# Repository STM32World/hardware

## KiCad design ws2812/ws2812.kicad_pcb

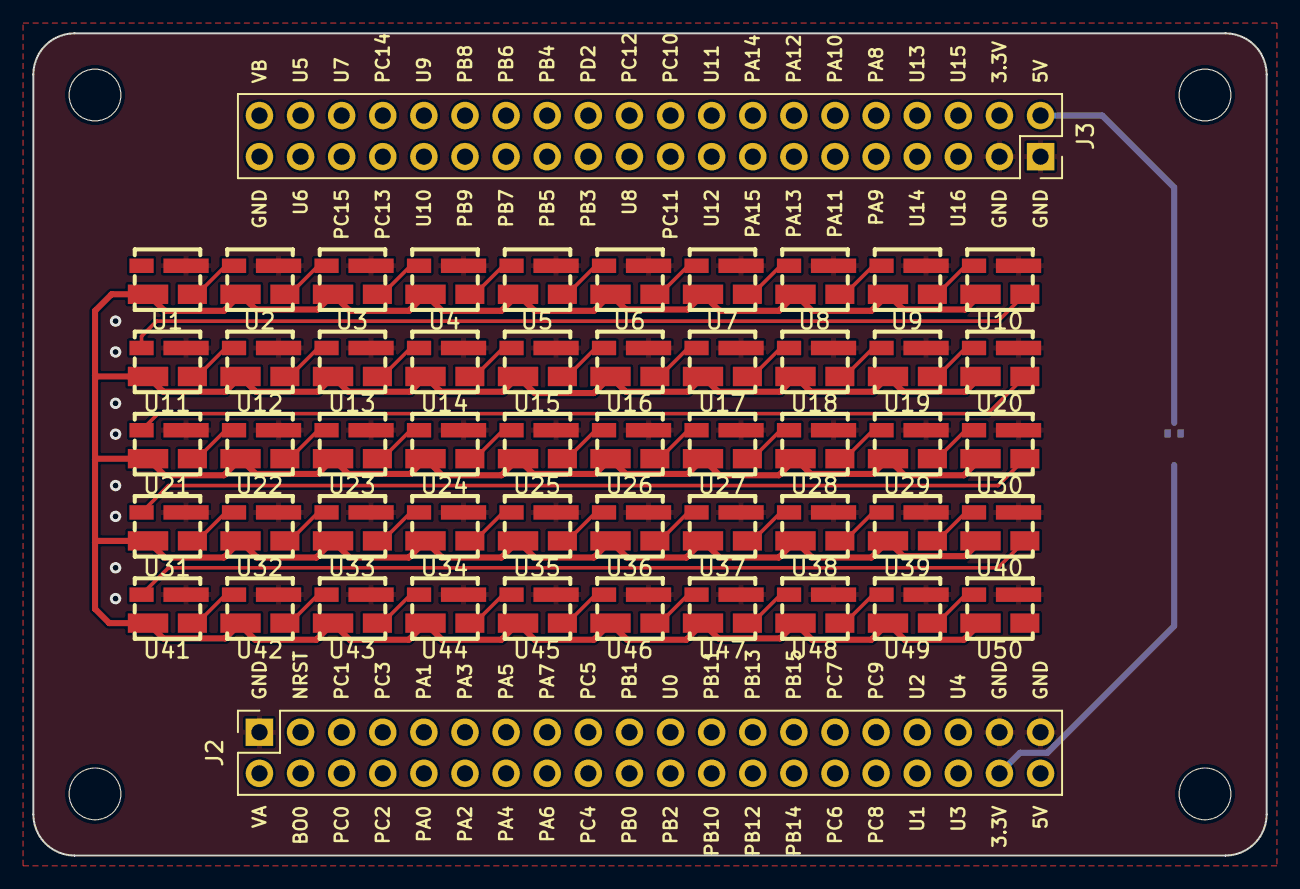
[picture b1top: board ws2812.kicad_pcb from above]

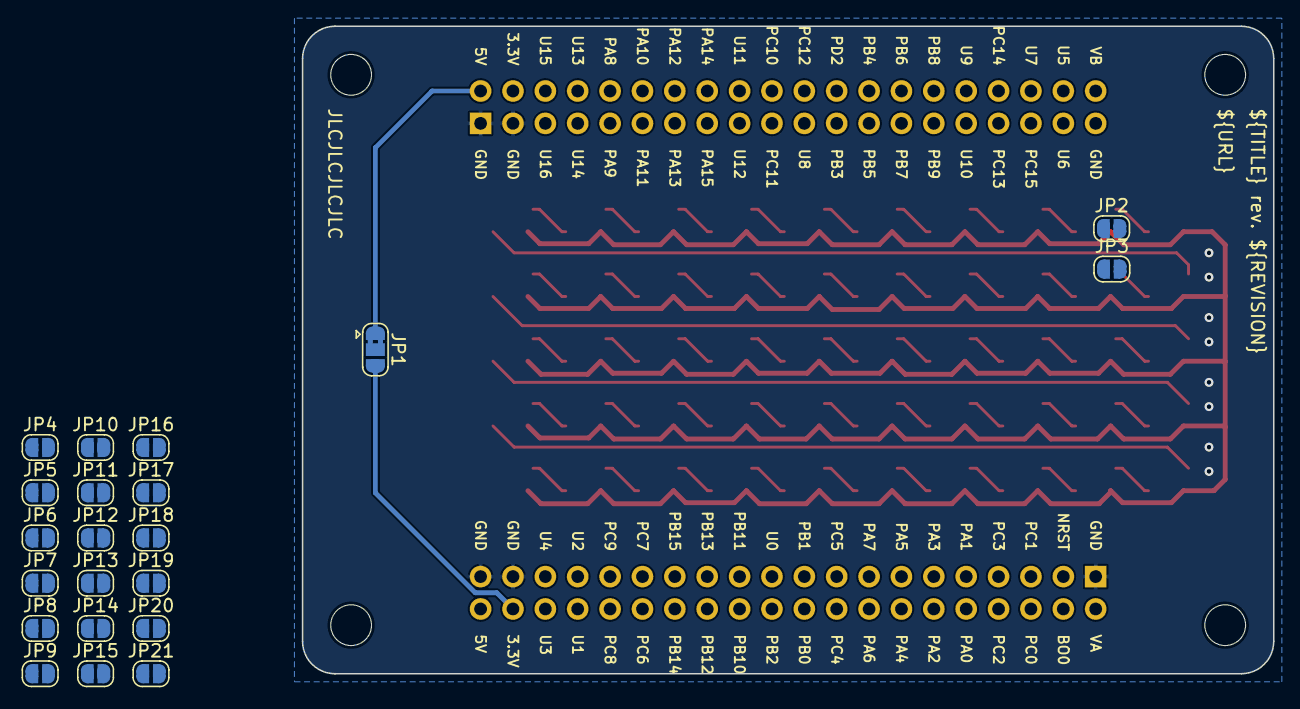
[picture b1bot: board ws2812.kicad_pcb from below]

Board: 2 copper layers, 76.2 x 50.8 mm, 74 parts (21 on the bottom side), 70 nets.

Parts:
J1: STM32WORLD_BOARD
J2: STM32WORLD_CONNECTOR_1; PinSocket_2x20_P2.54mm_Vertical_Stackable
J3: STM32WORLD_CONNECTOR_2; PinSocket_2x20_P2.54mm_Vertical_Stackable
JP1: SolderJumper-3_P1.3mm_Bridged2Bar12_RoundedPad1.0x1.5mm
JP2, JP3, JP4, JP5, JP6, JP7, JP8, JP9, JP10, JP11, JP12, JP13, JP14, JP15, JP16, JP17, JP18, JP19, JP20, JP21: SolderJumper-2_P1.3mm_Open_RoundedPad1.0x1.5mm
U1, U2, U3, U4, U5, U6, U7, U8, U9, U10, U11, U12, U13, U14, U15, U16, U17, U18, U19, U20, U21, U22, U23, U24, U25, U26, U27, U28, U29, U30, U31, U32, U33, U34, U35, U36, U37, U38, U39, U40, U41, U42, U43, U44, U45, U46, U47, U48, U49, U50: WS2812E; LED-SMD_4P-L3.7-W3.5-P1.75-BR-SK6812MINI

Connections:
+3.3V: J2.38 (3.3V), J3.4 (3.3V), JP1.3 (B)
+5V: J2.40 (5V), J3.2 (5V), JP1.1 (A)
GND: J2.1 (GND), J2.37 (GND), J2.39 (GND), J3.1 (GND), J3.3 (GND), U1.4 (GND), U2.4 (GND), U3.4 (GND), U4.4 (GND), U5.4 (GND), U6.4 (GND), U7.4 (GND), U8.4 (GND), U9.4 (GND), U10.4 (GND), U11.4 (GND), U12.4 (GND), U13.4 (GND), U14.4 (GND), U15.4 (GND), U16.4 (GND), U17.4 (GND), U18.4 (GND), U19.4 (GND), U20.4 (GND), U21.4 (GND), U22.4 (GND), U23.4 (GND), U24.4 (GND), U25.4 (GND), U26.4 (GND), U27.4 (GND), U28.4 (GND), U29.4 (GND), U30.4 (GND), U31.4 (GND), U32.4 (GND), U33.4 (GND), U34.4 (GND), U35.4 (GND), U36.4 (GND), U37.4 (GND), U38.4 (GND), U39.4 (GND), U40.4 (GND), U41.4 (GND), U42.4 (GND), U43.4 (GND), U44.4 (GND), U45.4 (GND), U46.4 (GND), U47.4 (GND), U48.4 (GND), U49.4 (GND), U50.4 (GND)
LED: JP2.2 (B), JP3.2 (B), JP4.2 (B), JP5.2 (B), JP6.2 (B), JP7.2 (B), JP8.2 (B), JP9.2 (B), JP10.2 (B), JP11.2 (B), JP12.2 (B), JP13.2 (B), JP14.2 (B), JP15.2 (B), JP16.2 (B), JP17.2 (B), JP18.2 (B), JP19.2 (B), JP20.2 (B), JP21.2 (B), U1.1 (DI)
unnamed: U1.3 (DO), U2.1 (DI)
unnamed: U2.3 (DO), U3.1 (DI)
unnamed: U3.3 (DO), U4.1 (DI)
unnamed: U4.3 (DO), U5.1 (DI)
unnamed: U5.3 (DO), U6.1 (DI)
unnamed: U6.3 (DO), U7.1 (DI)
unnamed: U7.3 (DO), U8.1 (DI)
unnamed: U8.3 (DO), U9.1 (DI)
unnamed: U9.3 (DO), U10.1 (DI)
unnamed: U10.3 (DO), U11.1 (DI)
unnamed: U11.3 (DO), U12.1 (DI)
unnamed: U12.3 (DO), U13.1 (DI)
unnamed: U13.3 (DO), U14.1 (DI)
unnamed: U14.3 (DO), U15.1 (DI)
unnamed: U15.3 (DO), U16.1 (DI)
unnamed: U16.3 (DO), U17.1 (DI)
unnamed: U17.3 (DO), U18.1 (DI)
unnamed: U18.3 (DO), U19.1 (DI)
unnamed: U19.3 (DO), U20.1 (DI)
unnamed: U20.3 (DO), U21.1 (DI)
unnamed: U21.3 (DO), U22.1 (DI)
unnamed: U22.3 (DO), U23.1 (DI)
unnamed: U23.3 (DO), U24.1 (DI)
unnamed: U24.3 (DO), U25.1 (DI)
unnamed: U25.3 (DO), U26.1 (DI)
unnamed: U26.3 (DO), U27.1 (DI)
unnamed: U27.3 (DO), U28.1 (DI)
unnamed: U28.3 (DO), U29.1 (DI)
unnamed: U29.3 (DO), U30.1 (DI)
unnamed: U30.3 (DO), U31.1 (DI)
unnamed: U31.3 (DO), U32.1 (DI)
unnamed: U32.3 (DO), U33.1 (DI)
unnamed: U33.3 (DO), U34.1 (DI)
unnamed: U34.3 (DO), U35.1 (DI)
unnamed: U35.3 (DO), U36.1 (DI)
unnamed: U36.3 (DO), U37.1 (DI)
unnamed: U37.3 (DO), U38.1 (DI)
unnamed: U38.3 (DO), U39.1 (DI)
unnamed: U39.3 (DO), U40.1 (DI)
unnamed: U40.3 (DO), U41.1 (DI)
unnamed: U41.3 (DO), U42.1 (DI)
unnamed: U42.3 (DO), U43.1 (DI)
unnamed: U43.3 (DO), U44.1 (DI)
unnamed: U44.3 (DO), U45.1 (DI)
unnamed: U45.3 (DO), U46.1 (DI)
unnamed: U46.3 (DO), U47.1 (DI)
unnamed: U47.3 (DO), U48.1 (DI)
unnamed: U48.3 (DO), U49.1 (DI)
unnamed: U49.3 (DO), U50.1 (DI)
TIM1_1: J3.10 (PA8), JP8.1 (A)
TIM1_2: J3.9 (PA9), JP9.1 (A)
TIM1_3: J3.12 (PA10), JP10.1 (A)
TIM1_4: J3.11 (PA11), JP11.1 (A)
TIM2_1: J3.15 (PA15), JP12.1 (A)
TIM2_2: J3.23 (PB3), JP13.1 (A)
TIM2_3: J2.24 (PB10), JP14.1 (A)
TIM2_4: J2.23 (PB11), JP15.1 (A)
TIM3_1: J2.30 (PC6), JP6.1 (A)
TIM3_2: J2.29 (PC7), JP7.1 (A)
TIM3_3: J2.32 (PC8), JP16.1 (A)
TIM3_4: J2.31 (PC9), JP17.1 (A)
TIM5_1: J2.10 (PA0), JP2.1 (A)
TIM5_2: J2.9 (PA1), JP3.1 (A)
TIM5_3: J2.12 (PA2), JP4.1 (A)
TIM5_4: J2.11 (PA3), JP5.1 (A)
VCC: JP1.2 (C), U1.2 (VDD), U2.2 (VDD), U3.2 (VDD), U4.2 (VDD), U5.2 (VDD), U6.2 (VDD), U7.2 (VDD), U8.2 (VDD), U9.2 (VDD), U10.2 (VDD), U11.2 (VDD), U12.2 (VDD), U13.2 (VDD), U14.2 (VDD), U15.2 (VDD), U16.2 (VDD), U17.2 (VDD), U18.2 (VDD), U19.2 (VDD), U20.2 (VDD), U21.2 (VDD), U22.2 (VDD), U23.2 (VDD), U24.2 (VDD), U25.2 (VDD), U26.2 (VDD), U27.2 (VDD), U28.2 (VDD), U29.2 (VDD), U30.2 (VDD), U31.2 (VDD), U32.2 (VDD), U33.2 (VDD), U34.2 (VDD), U35.2 (VDD), U36.2 (VDD), U37.2 (VDD), U38.2 (VDD), U39.2 (VDD), U40.2 (VDD), U41.2 (VDD), U42.2 (VDD), U43.2 (VDD), U44.2 (VDD), U45.2 (VDD), U46.2 (VDD), U47.2 (VDD), U48.2 (VDD), U49.2 (VDD), U50.2 (VDD)

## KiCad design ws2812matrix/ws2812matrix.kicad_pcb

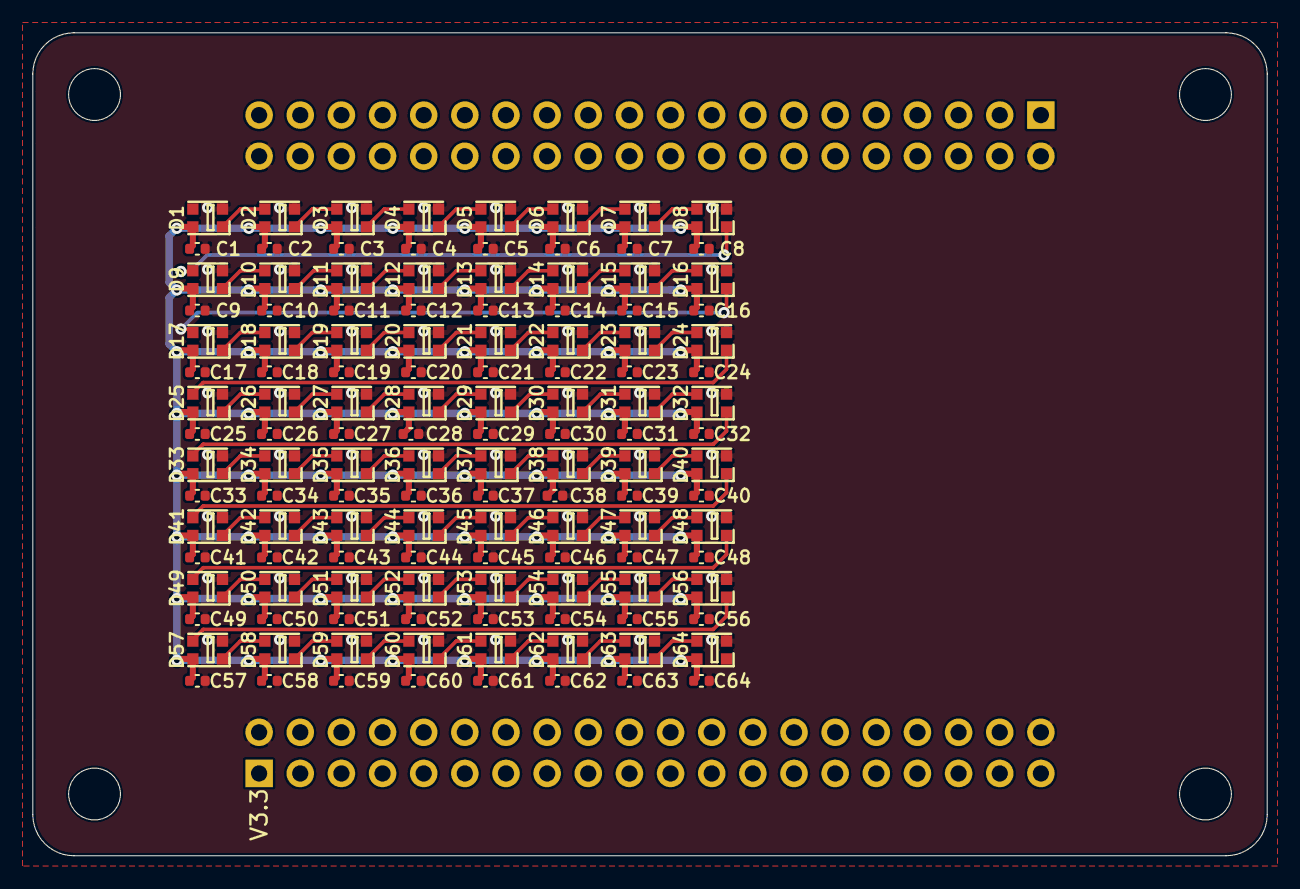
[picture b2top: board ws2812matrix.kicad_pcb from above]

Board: 2 copper layers, 76.2 x 50.8 mm, 129 parts (0 on the bottom side), 65 nets.

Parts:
C1, C2, C3, C4, C5, C6, C7, C8, C9, C10, C11, C12, C13, C14, C15, C16, C17, C18, C19, C20, C21, C22, C23, C24, C25, C26, C27, C28, C29, C30, C31, C32, C33, C34, C35, C36, C37, C38, C39, C40, C41, C42, C43, C44, C45, C46, C47, C48, C49, C50, C51, C52, C53, C54, C55, C56, C57, C58, C59, C60, C61, C62, C63, C64: 100nF; C_0402_1005Metric
D1, D2, D3, D4, D5, D6, D7, D8, D9, D10, D11, D12, D13, D14, D15, D16, D17, D18, D19, D20, D21, D22, D23, D24, D25, D26, D27, D28, D29, D30, D31, D32, D33, D34, D35, D36, D37, D38, D39, D40, D41, D42, D43, D44, D45, D46, D47, D48, D49, D50, D51, D52, D53, D54, D55, D56, D57, D58, D59, D60, D61, D62, D63, D64: WS2812; LED_WS2812C-2020
J1: STM32WORLD_BASE

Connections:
+5V: C1.1, C2.1, C3.1, C4.1, C5.1, C6.1, C7.1, C8.1, C9.1, C10.1, C11.1, C12.1, C13.1, C14.1, C15.1, C16.1, C17.1, C18.1, C19.1, C20.1, C21.1, C22.1, C23.1, C24.1, C25.1, C26.1, C27.1, C28.1, C29.1, C30.1, C31.1, C32.1, C33.1, C34.1, C35.1, C36.1, C37.1, C38.1, C39.1, C40.1, C41.1, C42.1, C43.1, C44.1, C45.1, C46.1, C47.1, C48.1, C49.1, C50.1, C51.1, C52.1, C53.1, C54.1, C55.1, C56.1, C57.1, C58.1, C59.1, C60.1, C61.1, C62.1, C63.1, C64.1, D1.4, D2.4, D3.4, D4.4, D5.4, D6.4, D7.4, D8.4, D9.4, D10.4, D11.4, D12.4, D13.4, D14.4, D15.4, D16.4, D17.4, D18.4, D19.4, D20.4, D21.4, D22.4, D23.4, D24.4, D25.4, D26.4, D27.4, D28.4, D29.4, D30.4, D31.4, D32.4, D33.4, D34.4, D35.4, D36.4, D37.4, D38.4, D39.4, D40.4, D41.4, D42.4, D43.4, D44.4, D45.4, D46.4, D47.4, D48.4, D49.4, D50.4, D51.4, D52.4, D53.4, D54.4, D55.4, D56.4, D57.4, D58.4, D59.4, D60.4, D61.4, D62.4, D63.4, D64.4
GND: C1.2, C2.2, C3.2, C4.2, C5.2, C6.2, C7.2, C8.2, C9.2, C10.2, C11.2, C12.2, C13.2, C14.2, C15.2, C16.2, C17.2, C18.2, C19.2, C20.2, C21.2, C22.2, C23.2, C24.2, C25.2, C26.2, C27.2, C28.2, C29.2, C30.2, C31.2, C32.2, C33.2, C34.2, C35.2, C36.2, C37.2, C38.2, C39.2, C40.2, C41.2, C42.2, C43.2, C44.2, C45.2, C46.2, C47.2, C48.2, C49.2, C50.2, C51.2, C52.2, C53.2, C54.2, C55.2, C56.2, C57.2, C58.2, C59.2, C60.2, C61.2, C62.2, C63.2, C64.2, D1.2, D2.2, D3.2, D4.2, D5.2, D6.2, D7.2, D8.2, D9.2, D10.2, D11.2, D12.2, D13.2, D14.2, D15.2, D16.2, D17.2, D18.2, D19.2, D20.2, D21.2, D22.2, D23.2, D24.2, D25.2, D26.2, D27.2, D28.2, D29.2, D30.2, D31.2, D32.2, D33.2, D34.2, D35.2, D36.2, D37.2, D38.2, D39.2, D40.2, D41.2, D42.2, D43.2, D44.2, D45.2, D46.2, D47.2, D48.2, D49.2, D50.2, D51.2, D52.2, D53.2, D54.2, D55.2, D56.2, D57.2, D58.2, D59.2, D60.2, D61.2, D62.2, D63.2, D64.2, J1.2, J1.40, J1.42, J1.80
unnamed: D1.1, D2.3
unnamed: D2.1, D3.3
unnamed: D3.1, D4.3
unnamed: D4.1, D5.3
unnamed: D5.1, D6.3
unnamed: D6.1, D7.3
unnamed: D7.1, D8.3
unnamed: D8.1, D9.3
unnamed: D10.1, D11.3
unnamed: D9.1, D10.3
unnamed: D11.1, D12.3
unnamed: D12.1, D13.3
unnamed: D13.1, D14.3
unnamed: D14.1, D15.3
unnamed: D15.1, D16.3
unnamed: D16.1, D17.3
unnamed: D17.1, D18.3
unnamed: D18.1, D19.3
unnamed: D19.1, D20.3
unnamed: D20.1, D21.3
unnamed: D21.1, D22.3
unnamed: D22.1, D23.3
unnamed: D23.1, D24.3
unnamed: D24.1, D25.3
unnamed: D25.1, D26.3
unnamed: D26.1, D27.3
unnamed: D27.1, D28.3
unnamed: D28.1, D29.3
unnamed: D29.1, D30.3
unnamed: D30.1, D31.3
unnamed: D31.1, D32.3
unnamed: D32.1, D33.3
unnamed: D33.1, D34.3
unnamed: D34.1, D35.3
unnamed: D35.1, D36.3
unnamed: D36.1, D37.3
unnamed: D37.1, D38.3
unnamed: D38.1, D39.3
unnamed: D39.1, D40.3
unnamed: D40.1, D41.3
unnamed: D41.1, D42.3
unnamed: D42.1, D43.3
unnamed: D43.1, D44.3
unnamed: D44.1, D45.3
unnamed: D45.1, D46.3
unnamed: D46.1, D47.3
unnamed: D47.1, D48.3
unnamed: D48.1, D49.3
unnamed: D49.1, D50.3
unnamed: D50.1, D51.3
unnamed: D51.1, D52.3
unnamed: D52.1, D53.3
unnamed: D53.1, D54.3
unnamed: D54.1, D55.3
unnamed: D55.1, D56.3
unnamed: D56.1, D57.3
unnamed: D57.1, D58.3
unnamed: D58.1, D59.3
unnamed: D59.1, D60.3
unnamed: D60.1, D61.3
unnamed: D61.1, D62.3
unnamed: D62.1, D63.3
unnamed: D63.1, D64.3
